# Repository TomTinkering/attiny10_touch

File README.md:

# attiny10_touch
simple single touch button based around attiny10 with soft uart.

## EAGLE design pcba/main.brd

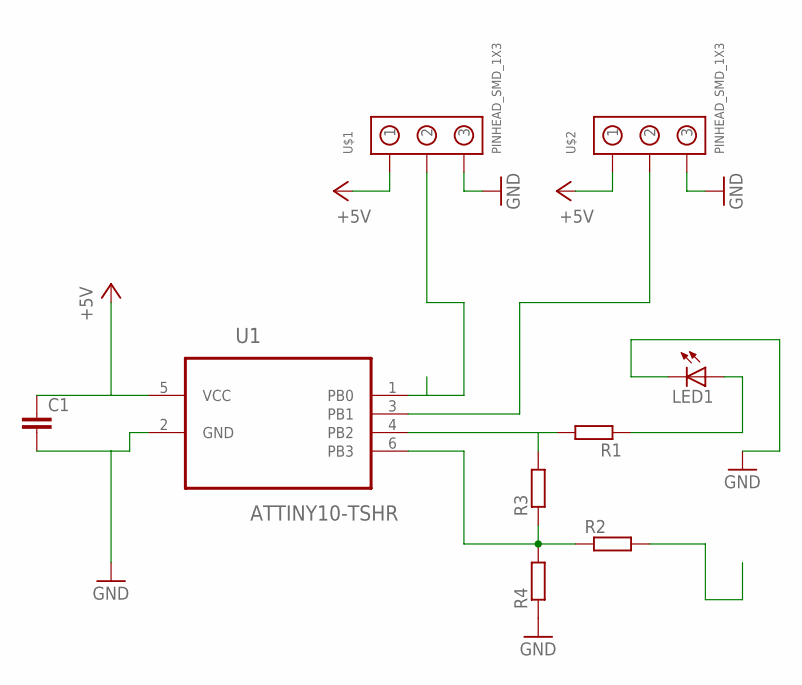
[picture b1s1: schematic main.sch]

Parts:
C1: C-EUC0805K; C0805K
LED1: LED_LEDP-LCC-2-BACK; LED_HOLE_4MM
R1, R2, R3, R4: R-EU_R0603; R0603
U1: ATTINY10-TSHR; SOT95P280X145-6N
U$1, U$2: PINHEAD_SMD_1X3; PINHEAD_1X3

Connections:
+5V: C1.1, U1.5 (VCC), U$1.P$1 (1), U$2.P$1 (1)
GND: C1.2, LED1.C, R4.1, U1.2 (GND), U$1.P$3 (3), U$2.P$3 (3)
unnamed: LED1.A, R1.1
unnamed: R1.2, R3.2, U1.4 (PB2)
unnamed: U1.3 (PB1), U$2.P$2 (2)
unnamed: U1.1 (PB0), U$1.P$2 (2)
unnamed: R2.1, R3.1, R4.2, U1.6 (PB3)
TOUCH_PAD: R2.2

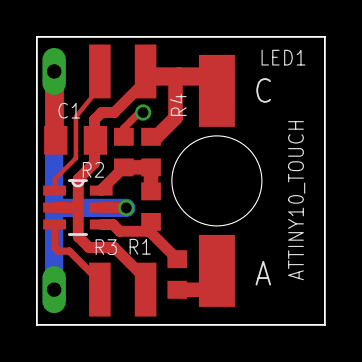
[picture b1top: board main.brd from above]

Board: 2 copper layers, 16.0 x 16.0 mm, 9 parts (0 on the bottom side), 7 nets.

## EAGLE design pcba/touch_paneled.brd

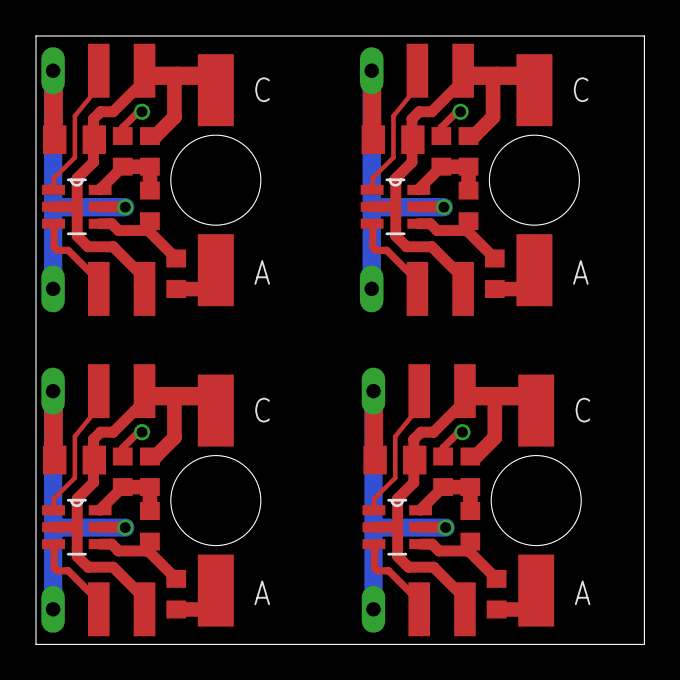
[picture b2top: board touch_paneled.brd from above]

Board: 2 copper layers, 33.8 x 33.8 mm, 36 parts (0 on the bottom side), 28 nets.

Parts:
C1, C2, C3, C4: C0805K
LED1, LED2, LED3, LED4: LED_HOLE_4MM
R1, R2, R3, R4, R5, R6, R7, R8, R9, R10, R11, R12, R13, R14, R15, R16: R0603
U1, U2, U3, U4: ATTINY10-TSHR; SOT95P280X145-6N
U$1, U$2, U$3, U$4, U$5, U$6, U$7, U$8: PINHEAD_SMD_1X3; PINHEAD_1X3

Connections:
+5V: C1.1, U1.5, U$1.P$1, U$2.P$1
+5V1: C2.1, U2.5, U$3.P$1, U$4.P$1
+5V2: C3.1, U3.5, U$5.P$1, U$6.P$1
+5V3: C4.1, U4.5, U$7.P$1, U$8.P$1
GND: C1.2, LED1.C, R4.1, U1.2, U$1.P$3, U$2.P$3
GND1: C2.2, LED2.C, R7.1, U2.2, U$3.P$3, U$4.P$3
GND2: C3.2, LED3.C, R11.1, U3.2, U$5.P$3, U$6.P$3
GND3: C4.2, LED4.C, R15.1, U4.2, U$7.P$3, U$8.P$3
unnamed: LED1.A, R1.1
unnamed: U2.3, U$4.P$2
unnamed: R1.2, R3.2, U1.4
unnamed: U2.1, U$3.P$2
unnamed: U1.3, U$2.P$2
unnamed: U1.1, U$1.P$2
unnamed: R5.1, R6.1, R7.2, U2.6
unnamed: R6.2, R8.2, U2.4
unnamed: LED2.A, R8.1
unnamed: R2.1, R3.1, R4.2, U1.6
unnamed: U3.3, U$6.P$2
unnamed: U3.1, U$5.P$2
unnamed: R9.1, R10.1, R11.2, U3.6
unnamed: R10.2, R12.2, U3.4
unnamed: LED3.A, R12.1
unnamed: U4.3, U$8.P$2
unnamed: U4.1, U$7.P$2
unnamed: R13.1, R14.1, R15.2, U4.6
unnamed: R14.2, R16.2, U4.4
unnamed: LED4.A, R16.1

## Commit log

2015-02-22 initial commit2
2015-02-22 worked on rudumentary uart implementation to estimate code size
2015-02-23 removed toolchain binary, added communication scheme documents
2015-02-25 working on bare-bone interrupt implementations
2015-02-26 finished interrupt implementations
2015-02-27 worked on uart implementation, getting there
2015-02-27 reduced T_OVF interrupt to two instructions ^^
2015-02-27 working on init function. Timer mode has to be normal for fixed 0xFFFF timer top. So PWM is made by clearing OCA0 pin on timer overflow, and setting it on compA match...
2015-02-27 defined state and message bit positions
2015-02-27 added some macro's, worked on init. Getting close, need to handle / store measurement values for touch... (low-pass etc.)
2015-02-28 implemented measurement processing stub (including low-pass). Low-pass takes ~100 isntructions.. optimizeable? Preparing to move uart processing into interrupt...
2015-02-28 moved uart processing to interrupt completely
2015-02-28 added simple excel sheet to show function of low-pass filter
2015-02-28 finished first draft of software, needs (a lot) of testing... Also, clean up code..
2015-03-02 started debugging uart, seems to work, though timing is an issue, might need another protocol...
2015-03-03 simple test running to design touch filters. See doc section. Clock inaccuracy might be a comms issue (+- 5% allow max).
2015-03-04 added simple spreadsheet to show effect of clock inaccracy on comms
